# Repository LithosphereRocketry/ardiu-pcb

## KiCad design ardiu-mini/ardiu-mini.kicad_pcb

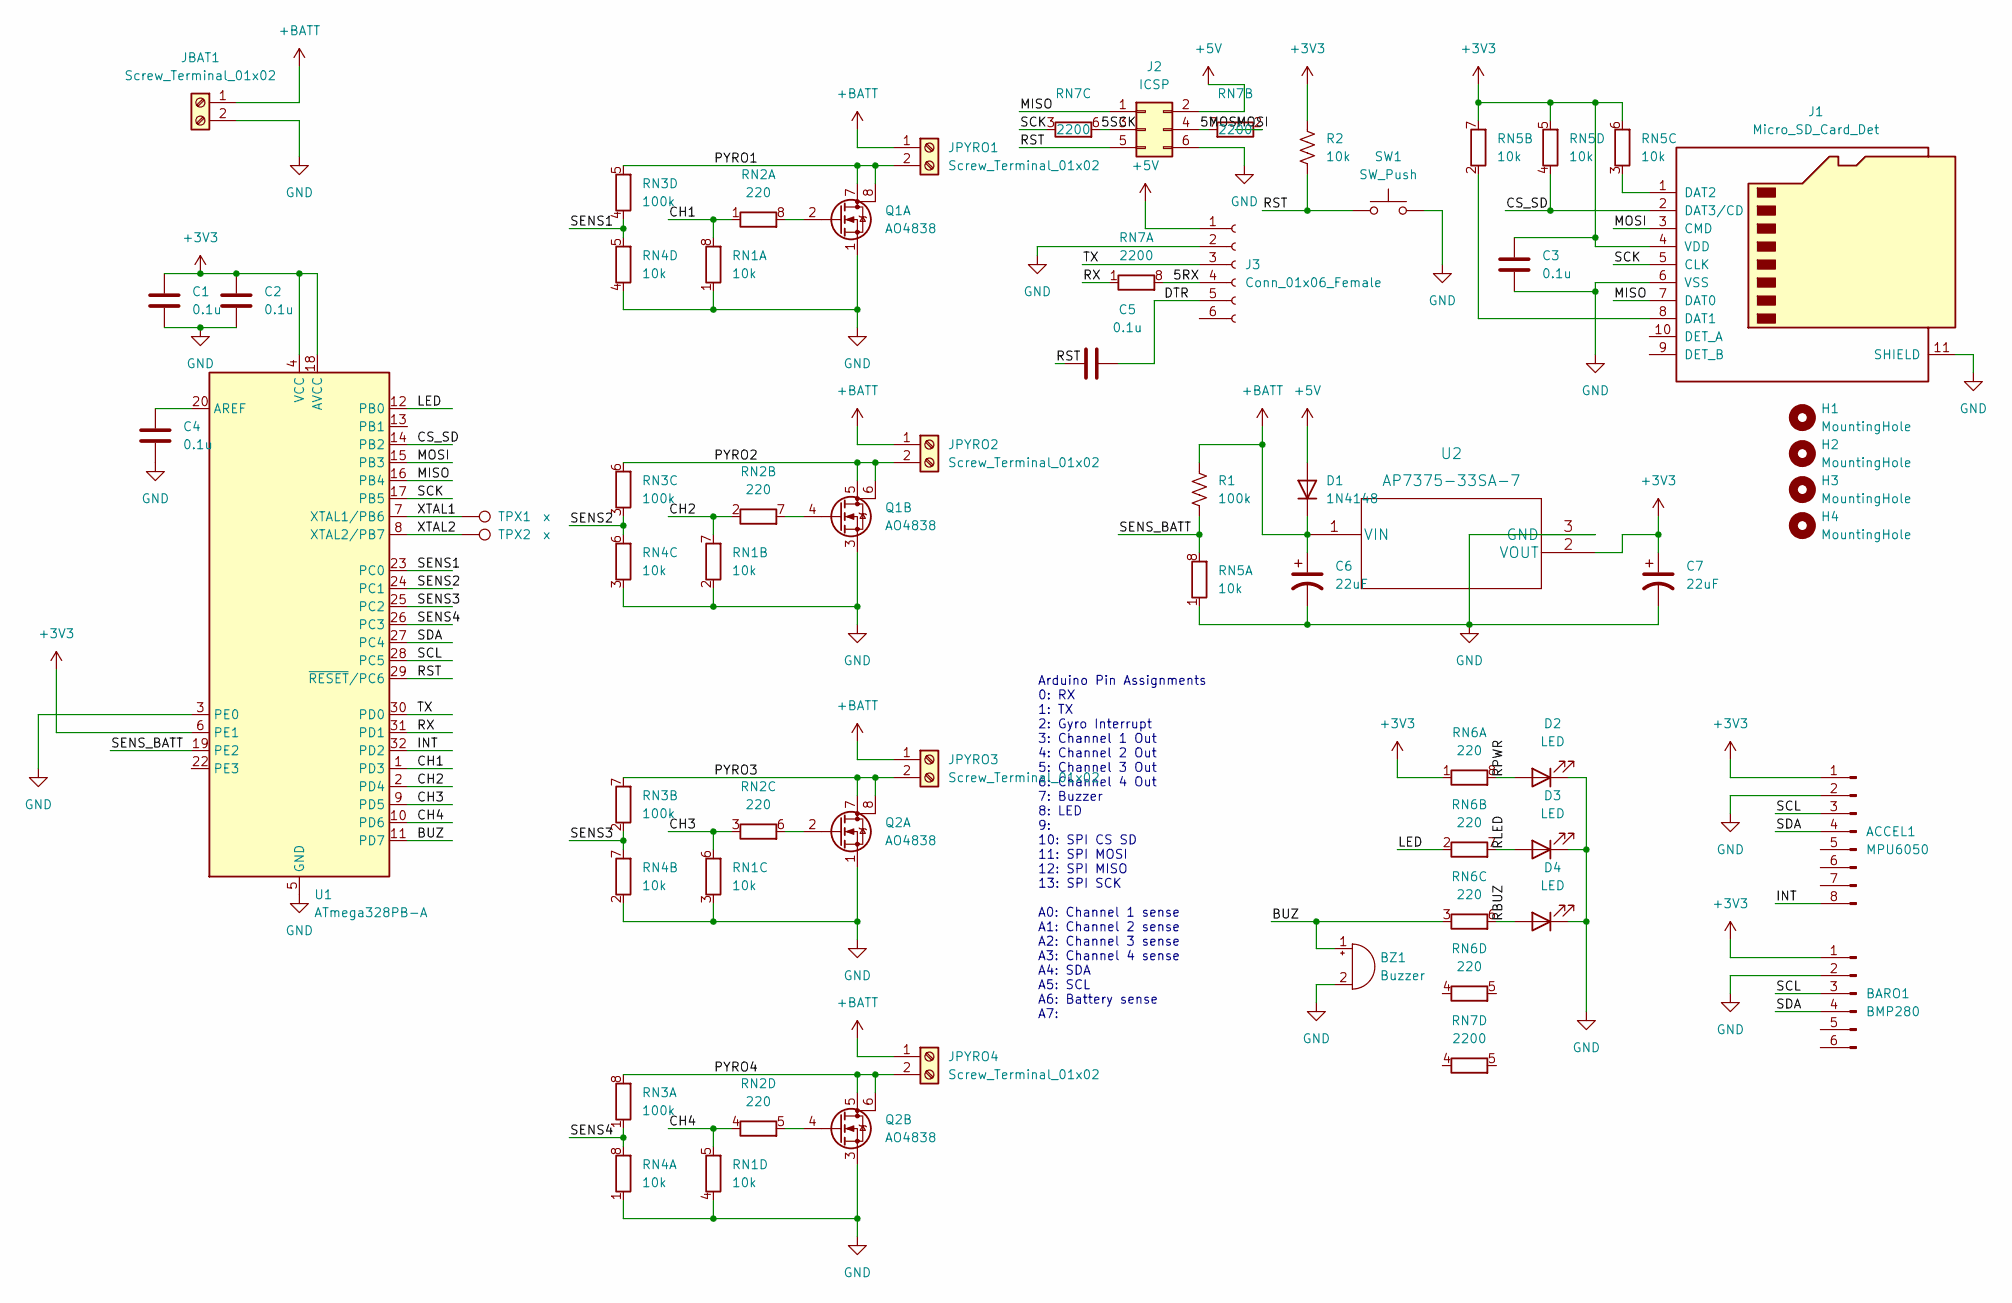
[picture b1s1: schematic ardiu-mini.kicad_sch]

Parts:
ACCEL1: MPU6050; Breakout_MPU6050_Generic
BARO1: BMP280; Breakout_BMP280_Generic
BZ1: Buzzer; Buzzer_12x9.5RM7.6
C1, C2, C3, C4, C5: 0.1u; C_0805_2012Metric_Pad1.18x1.45mm_HandSolder
C6, C7: 22uF; C_1206_3216Metric_Pad1.33x1.80mm_HandSolder
D1: 1N4148; D_DO-35_SOD27_P7.62mm_Horizontal
D2, D3, D4: LED; LED_D3.0mm
H1, H2, H3, H4: MountingHole; MountingHole_3.2mm_M3
J1: Micro_SD_Card_Det; Connector_Amphenol_MicroSD_PushPull
J2: ICSP; PinHeader_2x03_P2.54mm_Vertical
J3: Conn_01x06_Female; PinSocket_1x06_P2.54mm_Vertical
JBAT1: Screw_Terminal_01x02; TerminalBlock_TE_282834-2_1x02_P2.54mm_Horizontal
JPYRO1, JPYRO2, JPYRO3, JPYRO4: Screw_Terminal_01x02; TerminalBlock_TE_282834-2_1x02_P2.54mm_Horizontal
Q1, Q2: AO4838; SO-8_3.9x4.9mm_P1.27mm
R1: 100k; R_0805_2012Metric_Pad1.20x1.40mm_HandSolder
R2: 10k; R_0805_2012Metric_Pad1.20x1.40mm_HandSolder
RN1, RN4, RN5: 10k; R_Array_Concave_4x0603
RN2, RN6: 220; R_Array_Concave_4x0603
RN3: 100k; R_Array_Concave_4x0603
RN7: 2200; R_Array_Concave_4x0603
SW1: SW_Push; SW_PUSH_6mm
TPX1, TPX2: x; TestPoint_Pad_D1.5mm
U1: ATmega328PB-A; TQFP-32_7x7mm_P0.8mm
U2: AP7375-33SA-7; SOT-23_Handsoldering

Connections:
+3V3: ACCEL1.1, BARO1.1, C1.1, C2.1, C3.1, C7.1, J1.4 (VDD), R2.1, RN5.5 (R4.2), RN5.6 (R3.2), RN5.7 (R2.2), RN6.1 (R1.1), U1.4 (VCC), U1.6 (PE1), U1.18 (AVCC), U2.2 (VOUT)
+5V: D1.2 (A), J2.2, J3.1
+BATT: C6.1, D1.1 (K), JBAT1.1, JPYRO1.1, JPYRO2.1, JPYRO3.1, JPYRO4.1, R1.1, U2.1 (VIN)
/5MOSI: J2.4, RN7.7 (R2.2)
/5RX: J3.4, RN7.8 (R1.2)
/5SCK: J2.3, RN7.6 (R3.2)
/BUZ: BZ1.1 (-), RN6.3 (R3.1), U1.11 (PD7)
/CH1: RN1.8 (R1.2), RN2.1 (R1.1), U1.1 (PD3)
/CH2: RN1.7 (R2.2), RN2.2 (R2.1), U1.2 (PD4)
/CH3: RN1.6 (R3.2), RN2.3 (R3.1), U1.9 (PD5)
/CH4: RN1.5 (R4.2), RN2.4 (R4.1), U1.10 (PD6)
/CS_SD: J1.2 (DAT3/CD), RN5.4 (R4.1), U1.14 (PB2)
/DTR: C5.1, J3.5
/INT: ACCEL1.8, U1.32 (PD2)
/LED: RN6.2 (R2.1), U1.12 (PB0)
/MISO: J1.7 (DAT0), J2.1, U1.16 (PB4)
/MOSI: J1.3 (CMD), RN7.2 (R2.1), U1.15 (PB3)
/PYRO1: JPYRO1.2, Q1.7 (D), Q1.8 (D), RN3.5 (R4.2)
/PYRO2: JPYRO2.2, Q1.5 (D), Q1.6 (D), RN3.6 (R3.2)
/PYRO3: JPYRO3.2, Q2.7 (D), Q2.8 (D), RN3.7 (R2.2)
/PYRO4: JPYRO4.2, Q2.5 (D), Q2.6 (D), RN3.8 (R1.2)
/RBUZ: D4.2 (A), RN6.6 (R3.2)
/RLED: D3.2 (A), RN6.7 (R2.2)
/RPWR: D2.2 (A), RN6.8 (R1.2)
/RST: C5.2, J2.5, R2.2, SW1.1, U1.29 (~RESET/PC6)
/RX: RN7.1 (R1.1), U1.31 (PD1)
/SCK: J1.5 (CLK), RN7.3 (R3.1), U1.17 (PB5)
/SCL: ACCEL1.3, BARO1.3, U1.28 (PC5)
/SDA: ACCEL1.4, BARO1.4, U1.27 (PC4)
/SENS1: RN3.4 (R4.1), RN4.5 (R4.2), U1.23 (PC0)
/SENS2: RN3.3 (R3.1), RN4.6 (R3.2), U1.24 (PC1)
/SENS3: RN3.2 (R2.1), RN4.7 (R2.2), U1.25 (PC2)
/SENS4: RN3.1 (R1.1), RN4.8 (R1.2), U1.26 (PC3)
/SENS_BATT: R1.2, RN5.8 (R1.2), U1.19 (PE2)
/TX: J3.3, U1.30 (PD0)
/XTAL1: TPX1.1, U1.7 (XTAL1/PB6)
/XTAL2: TPX2.1, U1.8 (XTAL2/PB7)
GND: ACCEL1.2, BARO1.2, BZ1.2 (+), C1.2, C2.2, C3.2, C4.2, C6.2, C7.2, D2.1 (K), D3.1 (K), D4.1 (K), J1.6 (VSS), J1.11 (SHIELD), J2.6, J3.2, JBAT1.2, Q1.1 (S), Q1.3 (S), Q2.1 (S), Q2.3 (S), RN1.1 (R1.1), RN1.2 (R2.1), RN1.3 (R3.1), RN1.4 (R4.1), RN4.1 (R1.1), RN4.2 (R2.1), RN4.3 (R3.1), RN4.4 (R4.1), RN5.1 (R1.1), SW1.2, U1.3 (PE0), U1.5 (GND), U1.21 (GND), U2.3 (GND)
unnamed: C4.1, U1.20 (AREF)
unnamed: J1.1 (DAT2), RN5.3 (R3.1)
unnamed: J1.8 (DAT1), RN5.2 (R2.1)
unnamed: Q1.2 (G), RN2.8 (R1.2)
unnamed: Q1.4 (G), RN2.7 (R2.2)
unnamed: Q2.2 (G), RN2.6 (R3.2)
unnamed: Q2.4 (G), RN2.5 (R4.2)

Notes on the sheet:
Arduino Pin Assignments 0: RX 1: TX 2: Gyro Interrupt 3: Channel 1 Out 4: Channel 2 Out 5: Channel 3 Out 6: Channel 4 Out 7: Buzzer 8: LED 9: 10: SPI CS SD 11: SPI MOSI 12: SPI MISO 13: SPI SCK A0: Channel 1 sense A1: Channel 2 sense A2: Channel 3 sense A3: Channel 4 sense A4: SDA A5: SCL A6: Batte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

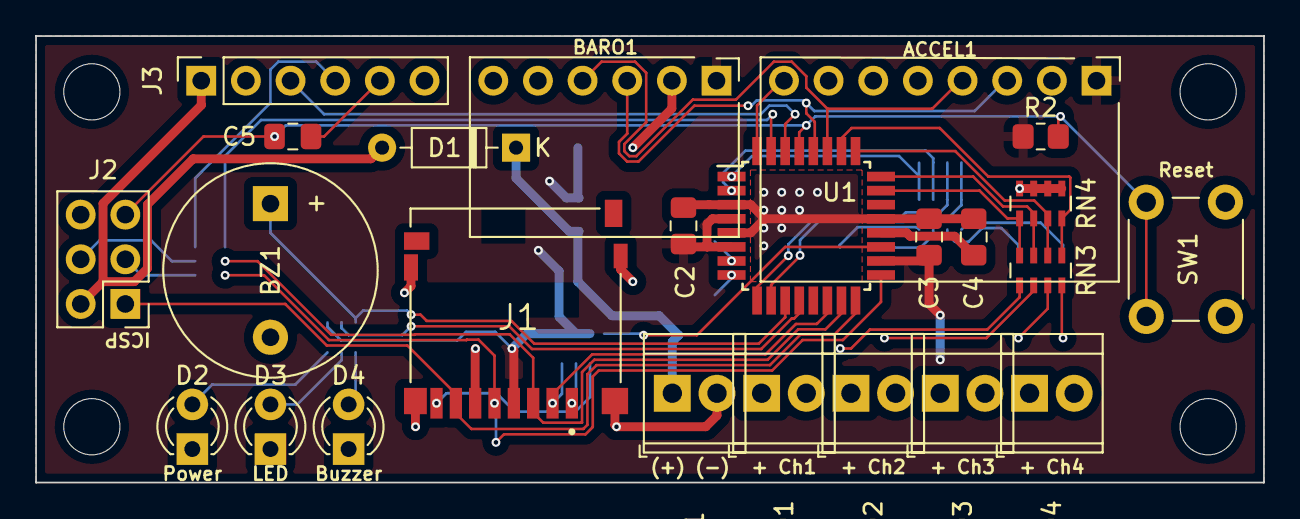
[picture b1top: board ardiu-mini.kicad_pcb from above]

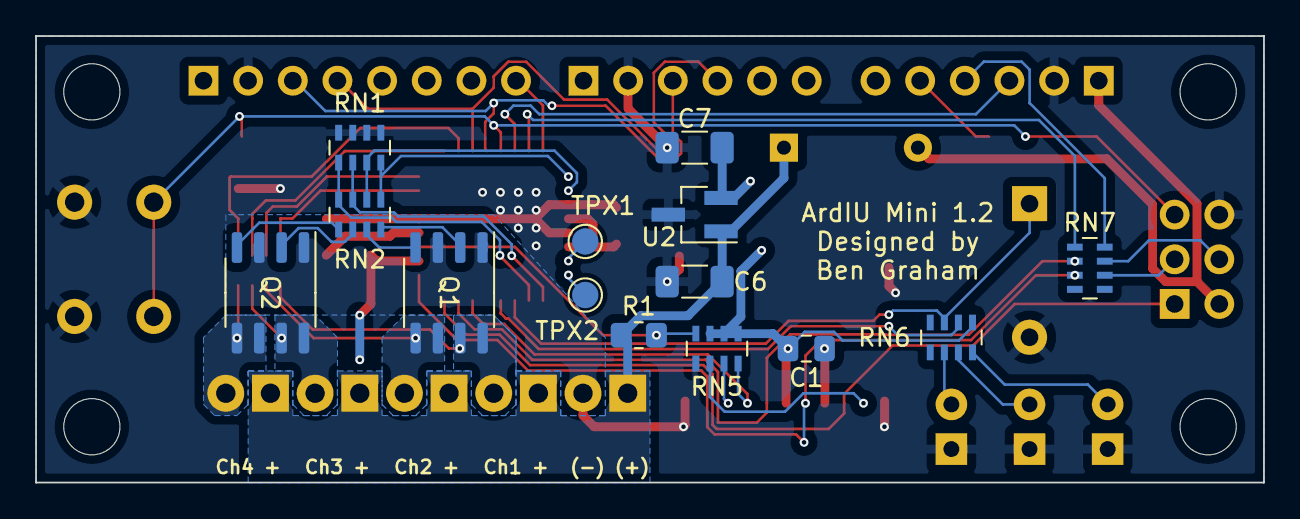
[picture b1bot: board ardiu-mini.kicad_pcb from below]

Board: 2 copper layers, 69.9 x 25.4 mm, 42 parts (14 on the bottom side), 45 nets.

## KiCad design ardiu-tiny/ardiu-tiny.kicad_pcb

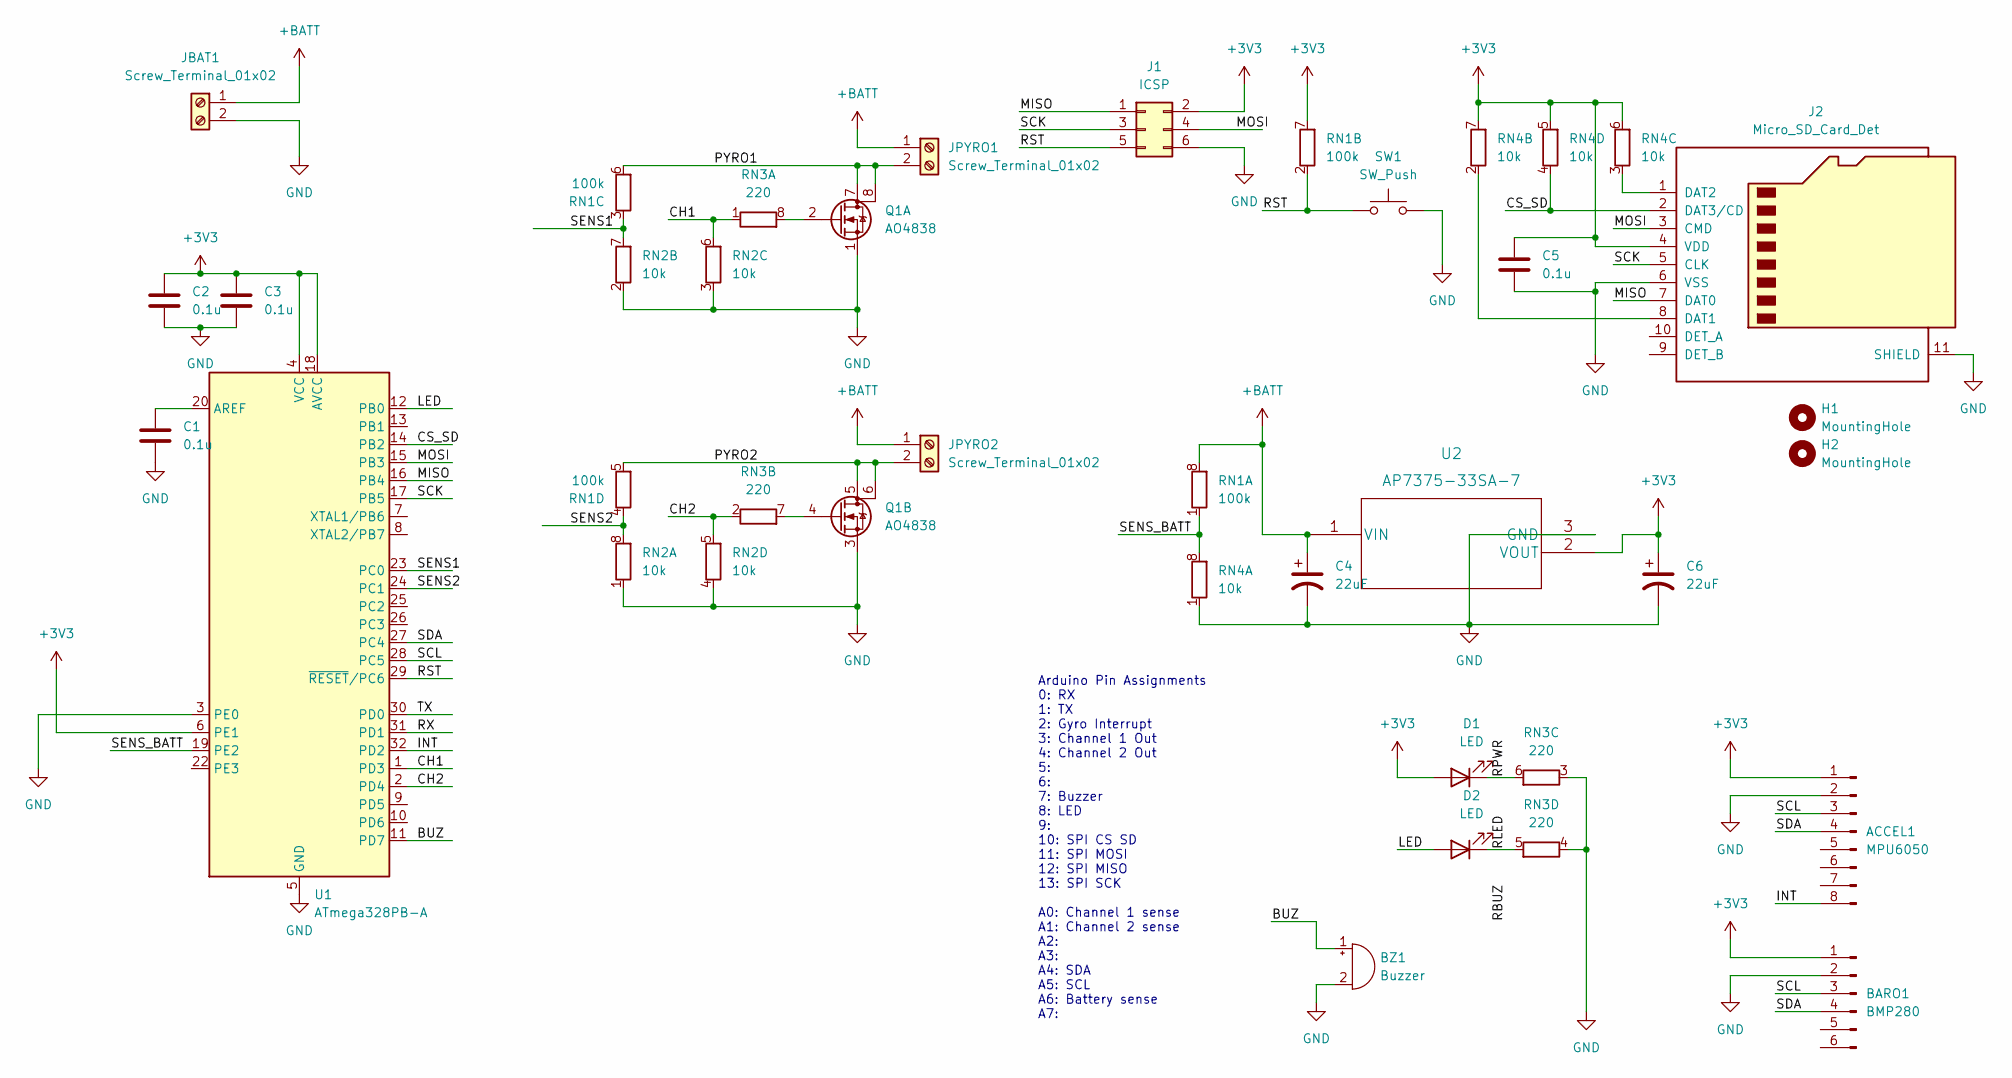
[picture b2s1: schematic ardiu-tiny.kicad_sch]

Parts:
ACCEL1: MPU6050; Breakout_MPU6050_Generic
BARO1: BMP280; Breakout_BMP280_Generic
BZ1: Buzzer; Buzzer_CUI_CPT-9019S-SMT
C1, C2, C3, C5: 0.1u; C_0805_2012Metric_Pad1.18x1.45mm_HandSolder
C4, C6: 22uF; C_1206_3216Metric_Pad1.33x1.80mm_HandSolder
D1, D2: LED; LED_1206_3216Metric_Pad1.42x1.75mm_HandSolder
H1, H2: MountingHole; MountingHole_3.2mm_M3
J1: ICSP; PinHeader_2x03_P2.54mm_Vertical
J2: Micro_SD_Card_Det; Connector_Amphenol_MicroSD_PushPull
JBAT1: Screw_Terminal_01x02; TerminalBlock_TE_282834-2_1x02_P2.54mm_Horizontal
JPYRO1, JPYRO2: Screw_Terminal_01x02; TerminalBlock_TE_282834-2_1x02_P2.54mm_Horizontal
Q1: AO4838; SO-8_3.9x4.9mm_P1.27mm
RN1: 100k; R_Array_Concave_4x0603
RN2, RN4: 10k; R_Array_Concave_4x0603
RN3: 220; R_Array_Concave_4x0603
SW1: SW_Push; SW_Push_Rect_5mm
U1: ATmega328PB-A; TQFP-32_7x7mm_P0.8mm
U2: AP7375-33SA-7; SOT-23_Handsoldering

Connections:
+3V3: ACCEL1.1, BARO1.1, C2.1, C3.1, C5.1, C6.1, D1.2 (A), J1.2, J2.4 (VDD), RN1.7 (R2.2), RN4.5 (R4.2), RN4.6 (R3.2), RN4.7 (R2.2), U1.4 (VCC), U1.6 (PE1), U1.18 (AVCC), U2.2 (VOUT)
+BATT: C4.1, JBAT1.1, JPYRO1.1, JPYRO2.1, RN1.8 (R1.2), U2.1 (VIN)
/BUZ: BZ1.1 (-), U1.11 (PD7)
/CH1: RN2.6 (R3.2), RN3.1 (R1.1), U1.1 (PD3)
/CH2: RN2.5 (R4.2), RN3.2 (R2.1), U1.2 (PD4)
/CS_SD: J2.2 (DAT3/CD), RN4.4 (R4.1), U1.14 (PB2)
/INT: ACCEL1.8, U1.32 (PD2)
/LED: D2.2 (A), U1.12 (PB0)
/MISO: J1.1, J2.7 (DAT0), U1.16 (PB4)
/MOSI: J1.4, J2.3 (CMD), U1.15 (PB3)
/PYRO1: JPYRO1.2, Q1.7 (D), Q1.8 (D), RN1.6 (R3.2)
/PYRO2: JPYRO2.2, Q1.5 (D), Q1.6 (D), RN1.5 (R4.2)
/RLED: D2.1 (K), RN3.5 (R4.2)
/RPWR: D1.1 (K), RN3.6 (R3.2)
/RST: J1.5, RN1.2 (R2.1), SW1.1, U1.29 (~RESET/PC6)
/RX: U1.31 (PD1)
/SCK: J1.3, J2.5 (CLK), U1.17 (PB5)
/SCL: ACCEL1.3, BARO1.3, U1.28 (PC5)
/SDA: ACCEL1.4, BARO1.4, U1.27 (PC4)
/SENS1: RN1.3 (R3.1), RN2.7 (R2.2), U1.23 (PC0)
/SENS2: RN1.4 (R4.1), RN2.8 (R1.2), U1.24 (PC1)
/SENS_BATT: RN1.1 (R1.1), RN4.8 (R1.2), U1.19 (PE2)
/TX: U1.30 (PD0)
GND: ACCEL1.2, BARO1.2, BZ1.2 (+), C1.2, C2.2, C3.2, C4.2, C5.2, C6.2, J1.6, J2.6 (VSS), J2.11 (SHIELD), JBAT1.2, Q1.1 (S), Q1.3 (S), RN2.1 (R1.1), RN2.2 (R2.1), RN2.3 (R3.1), RN2.4 (R4.1), RN3.3 (R3.1), RN3.4 (R4.1), RN4.1 (R1.1), SW1.2, U1.3 (PE0), U1.5 (GND), U1.21 (GND), U2.3 (GND)
unnamed: J2.8 (DAT1), RN4.2 (R2.1)
unnamed: J2.1 (DAT2), RN4.3 (R3.1)
unnamed: Q1.2 (G), RN3.8 (R1.2)
unnamed: Q1.4 (G), RN3.7 (R2.2)
unnamed: C1.1, U1.20 (AREF)

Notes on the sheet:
Arduino Pin Assignments 0: RX 1: TX 2: Gyro Interrupt 3: Channel 1 Out 4: Channel 2 Out 5: 6: 7: Buzzer 8: LED 9: 10: SPI CS SD 11: SPI MOSI 12: SPI MISO 13: SPI SCK A0: Channel 1 sense A1: Channel 2 sense A2: A3: A4: SDA A5: SCL A6: Battery sense A7:

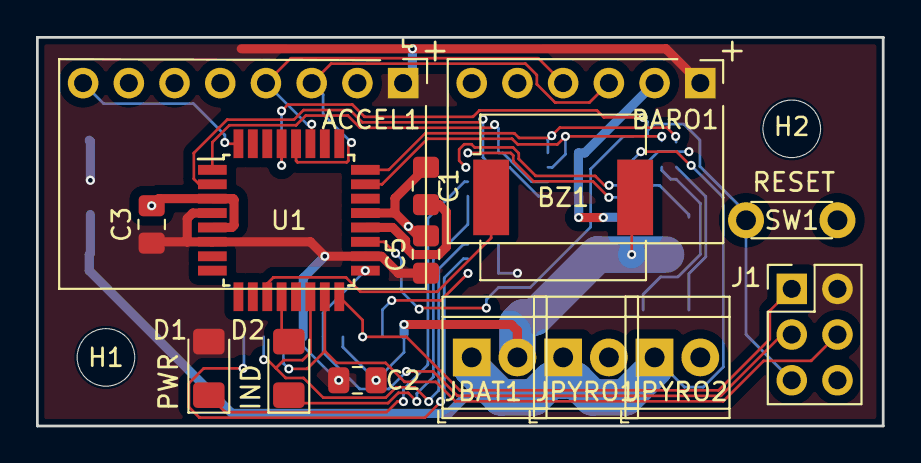
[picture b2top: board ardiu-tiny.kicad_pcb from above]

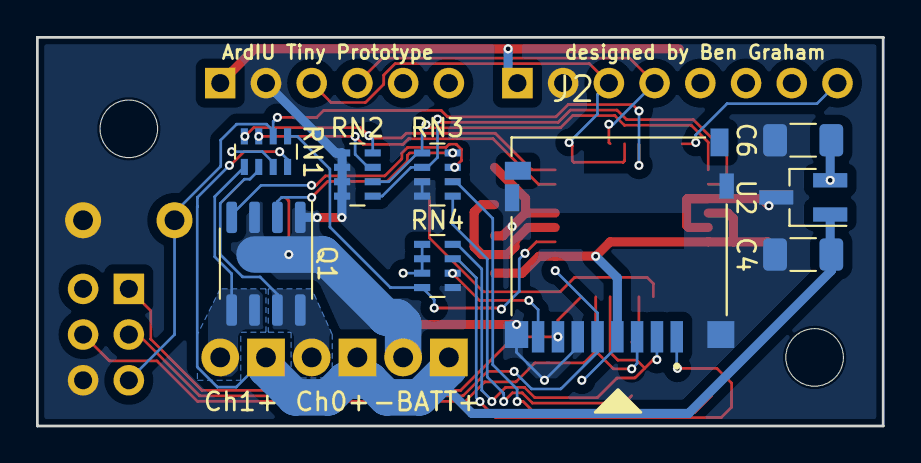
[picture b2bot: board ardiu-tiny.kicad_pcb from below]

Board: 2 copper layers, 47.0 x 21.6 mm, 26 parts (9 on the bottom side), 27 nets.

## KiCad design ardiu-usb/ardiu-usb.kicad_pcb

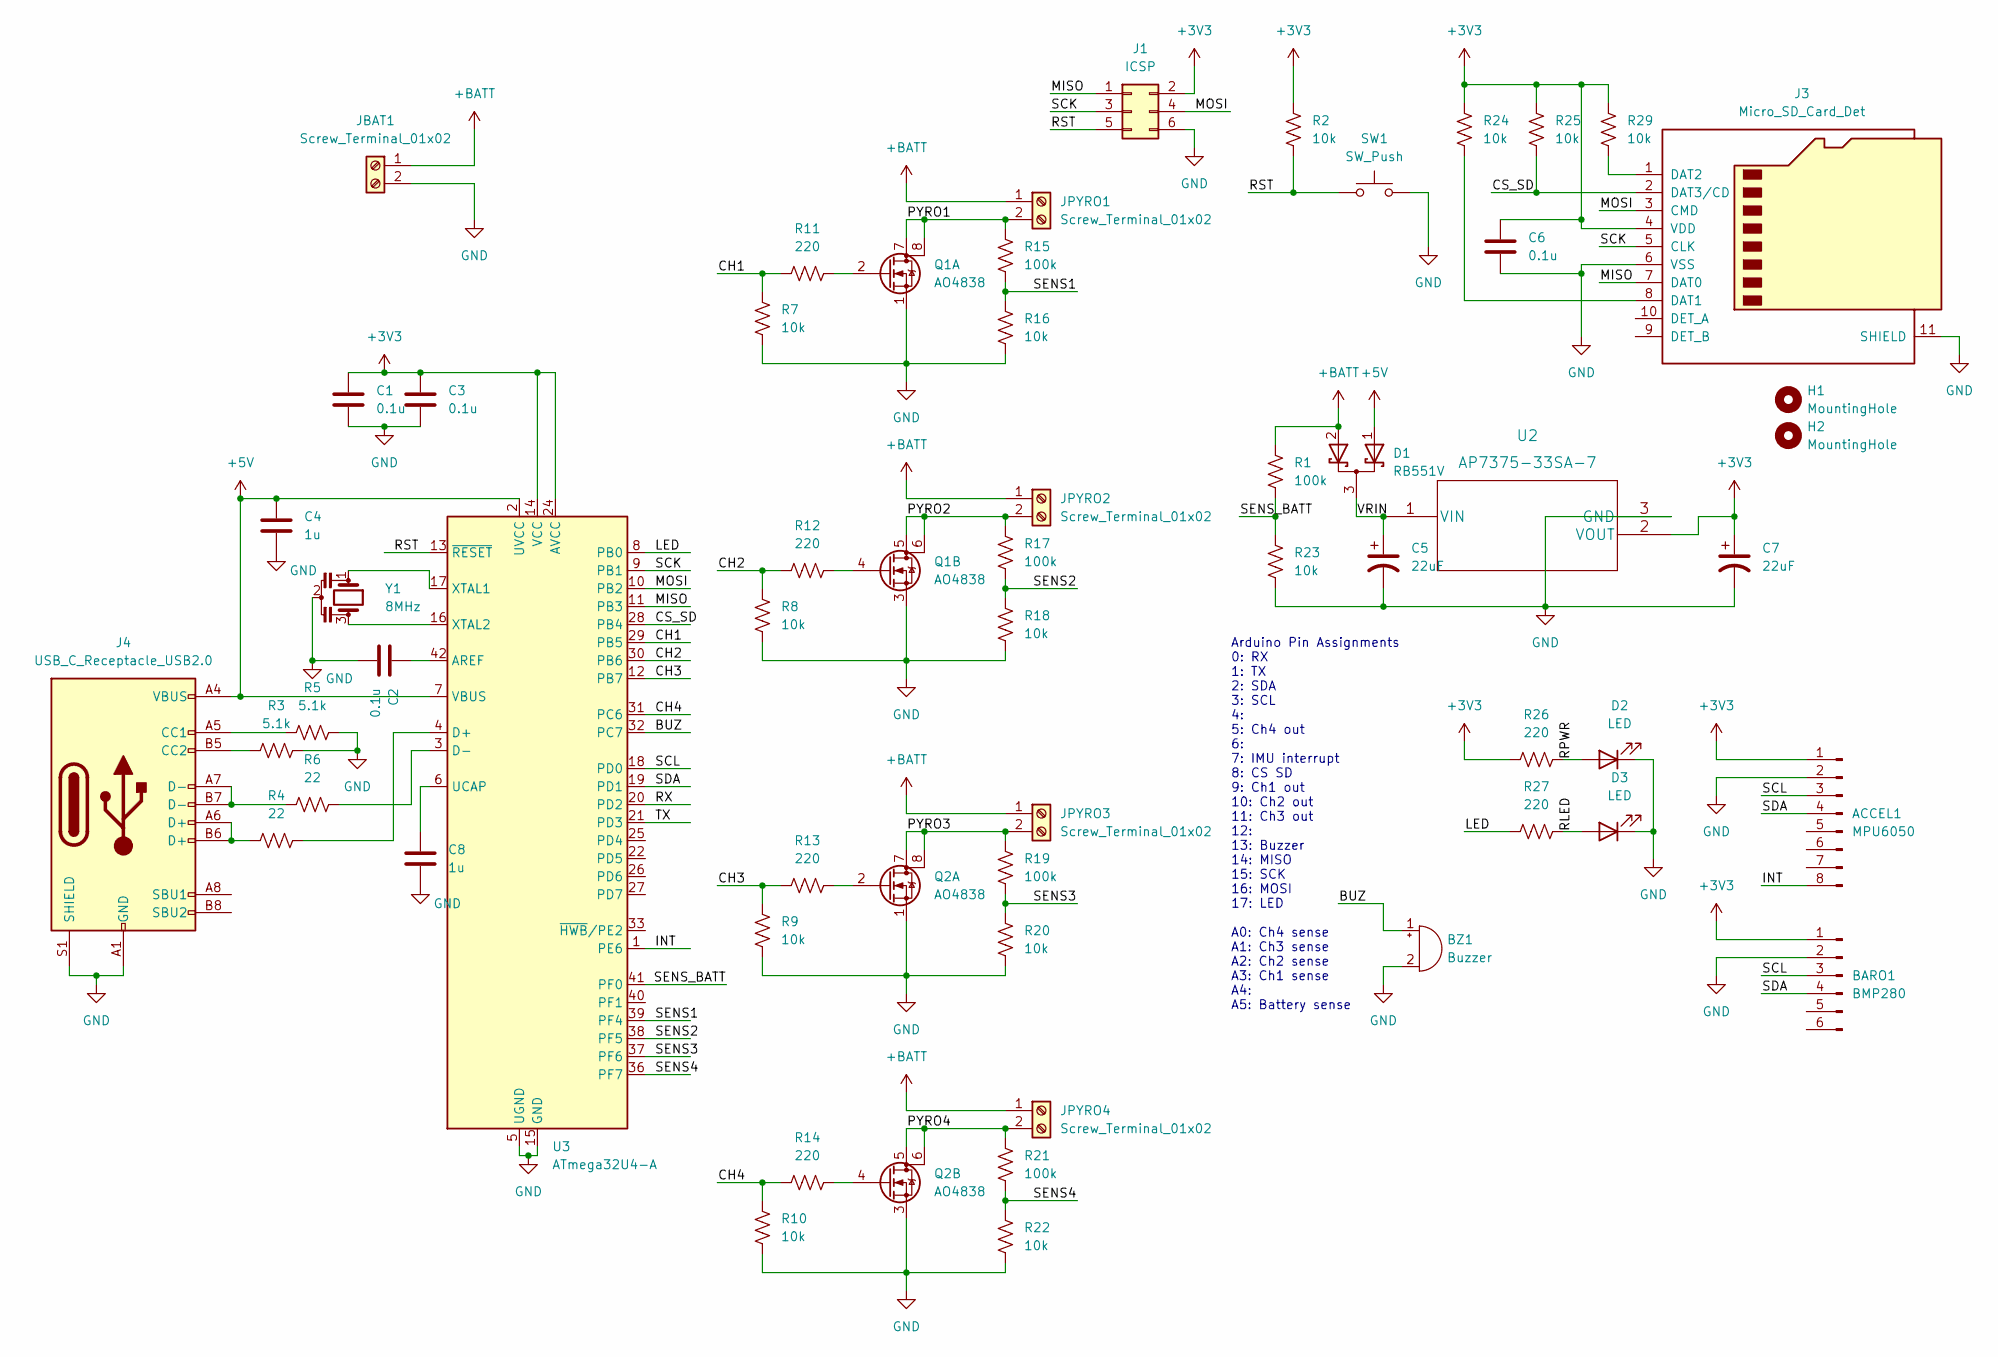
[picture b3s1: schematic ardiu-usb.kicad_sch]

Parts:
ACCEL1: MPU6050; Breakout_MPU6050_Generic
BARO1: BMP280; Breakout_BMP280_Generic
BZ1: Buzzer; Buzzer_12x9.5RM7.6
C1, C2, C3, C6: 0.1u; C_0805_2012Metric_Pad1.18x1.45mm_HandSolder
C4, C8: 1u; C_0805_2012Metric_Pad1.18x1.45mm_HandSolder
C5, C7: 22uF; C_1206_3216Metric_Pad1.33x1.80mm_HandSolder
D1: RB551V; SOT-23_Handsoldering
D2, D3: LED; LED_D3.0mm
H1, H2: MountingHole; MountingHole_3.2mm_M3
J1: ICSP; PinHeader_2x03_P2.54mm_Vertical
J3: Micro_SD_Card_Det; Connector_Amphenol_MicroSD_PushPull
J4: USB_C_Receptacle_USB2.0; USB_C_Receptacle_GCT_USB4085
JBAT1: Screw_Terminal_01x02; TerminalBlock_TE_282834-2_1x02_P2.54mm_Horizontal
JPYRO1, JPYRO2, JPYRO3, JPYRO4: Screw_Terminal_01x02; TerminalBlock_TE_282834-2_1x02_P2.54mm_Horizontal
Q1, Q2: AO4838; SO-8_3.9x4.9mm_P1.27mm
R1, R15, R17, R19, R21: 100k; R_0805_2012Metric_Pad1.20x1.40mm_HandSolder
R2, R7, R8, R9, R10, R16, R18, R20, R22, R23, R24, R25, R29: 10k; R_0805_2012Metric_Pad1.20x1.40mm_HandSolder
R3, R5: 5.1k; R_0805_2012Metric_Pad1.20x1.40mm_HandSolder
R4, R6: 22; R_0805_2012Metric_Pad1.20x1.40mm_HandSolder
R11, R12, R13, R14, R26, R27: 220; R_0805_2012Metric_Pad1.20x1.40mm_HandSolder
SW1: SW_Push; SW_PUSH_6mm
U2: AP7375-33SA-7; SOT-23_Handsoldering
U3: ATmega32U4-A; TQFP-44_10x10mm_P0.8mm
Y1: 8MHz; Resonator_SMD_Murata_CSTxExxV-3Pin_3.0x1.1mm_HandSoldering

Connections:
+3V3: ACCEL1.1, BARO1.1, C1.1, C3.1, C6.1, C7.1, J1.2, J3.4 (VDD), R2.1, R24.1, R25.1, R26.1, R29.1, U2.2 (VOUT), U3.14 (VCC), U3.24 (AVCC), U3.34 (VCC), U3.44 (AVCC)
+5V: C4.1, D1.1 (K), J4.A4 (VBUS), J4.A9 (VBUS), J4.B4 (VBUS), J4.B9 (VBUS), U3.2 (UVCC), U3.7 (VBUS)
+BATT: D1.2 (K), JBAT1.1, JPYRO1.1, JPYRO2.1, JPYRO3.1, JPYRO4.1, R1.1
/BUZ: BZ1.1 (-), U3.32 (PC7)
/CH1: R7.1, R11.1, U3.29 (PB5)
/CH2: R8.1, R12.1, U3.30 (PB6)
/CH3: R9.1, R13.1, U3.12 (PB7)
/CH4: R10.1, R14.1, U3.31 (PC6)
/CS_SD: J3.2 (DAT3/CD), R25.2, U3.28 (PB4)
/INT: ACCEL1.8, U3.1 (PE6)
/LED: R27.1, U3.8 (PB0)
/MISO: J1.1, J3.7 (DAT0), U3.11 (PB3)
/MOSI: J1.4, J3.3 (CMD), U3.10 (PB2)
/PYRO1: JPYRO1.2, Q1.7 (D), Q1.8 (D), R15.1
/PYRO2: JPYRO2.2, Q1.5 (D), Q1.6 (D), R17.1
/PYRO3: JPYRO3.2, Q2.7 (D), Q2.8 (D), R19.1
/PYRO4: JPYRO4.2, Q2.5 (D), Q2.6 (D), R21.1
/RLED: D3.2 (A), R27.2
/RPWR: D2.2 (A), R26.2
/RST: J1.5, R2.2, SW1.1, U3.13 (~RESET)
/RX: U3.20 (PD2)
/SCK: J1.3, J3.5 (CLK), U3.9 (PB1)
/SCL: ACCEL1.3, BARO1.3, U3.18 (PD0)
/SDA: ACCEL1.4, BARO1.4, U3.19 (PD1)
/SENS1: R15.2, R16.1, U3.39 (PF4)
/SENS2: R17.2, R18.1, U3.38 (PF5)
/SENS3: R19.2, R20.1, U3.37 (PF6)
/SENS4: R21.2, R22.1, U3.36 (PF7)
/SENS_BATT: R1.2, R23.1, U3.41 (PF0)
/TX: U3.21 (PD3)
/VRIN: C5.1, D1.3 (A), U2.1 (VIN)
GND: ACCEL1.2, BARO1.2, BZ1.2 (+), C1.2, C2.2, C3.2, C4.2, C5.2, C6.2, C7.2, C8.2, D2.1 (K), D3.1 (K), J1.6, J3.6 (VSS), J3.11 (SHIELD), J4.A1 (GND), J4.A12 (GND), J4.B1 (GND), J4.B12 (GND), J4.S1 (SHIELD), JBAT1.2, Q1.1 (S), Q1.3 (S), Q2.1 (S), Q2.3 (S), R3.2, R5.2, R7.2, R8.2, R9.2, R10.2, R16.2, R18.2, R20.2, R22.2, R23.2, SW1.2, U2.3 (GND), U3.5 (UGND), U3.15 (GND), U3.23 (GND), U3.35 (GND), U3.43 (GND), Y1.2
unnamed: C2.1, U3.42 (AREF)
unnamed: C8.1, U3.6 (UCAP)
unnamed: J3.1 (DAT2), R29.2
unnamed: J3.8 (DAT1), R24.2
unnamed: J4.A5 (CC1), R5.1
unnamed: J4.A6 (D+), J4.B6 (D+), R4.1
unnamed: J4.A7 (D-), J4.B7 (D-), R6.1
unnamed: J4.B5 (CC2), R3.1
unnamed: Q1.2 (G), R11.2
unnamed: Q1.4 (G), R12.2
unnamed: Q2.2 (G), R13.2
unnamed: Q2.4 (G), R14.2
unnamed: R4.2, U3.4 (D+)
unnamed: R6.2, U3.3 (D-)
unnamed: U3.16 (XTAL2), Y1.3
unnamed: U3.17 (XTAL1), Y1.1

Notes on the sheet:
Arduino Pin Assignments 0: RX 1: TX 2: SDA 3: SCL 4: 5: Ch4 out 6: 7: IMU interrupt 8: CS SD 9: Ch1 out 10: Ch2 out 11: Ch3 out 12: 13: Buzzer 14: MISO 15: SCK 16: MOSI 17: LED A0: Ch4 sense A1: Ch3 sense A2: Ch2 sense A3: Ch1 sense A4: A5: Battery sense

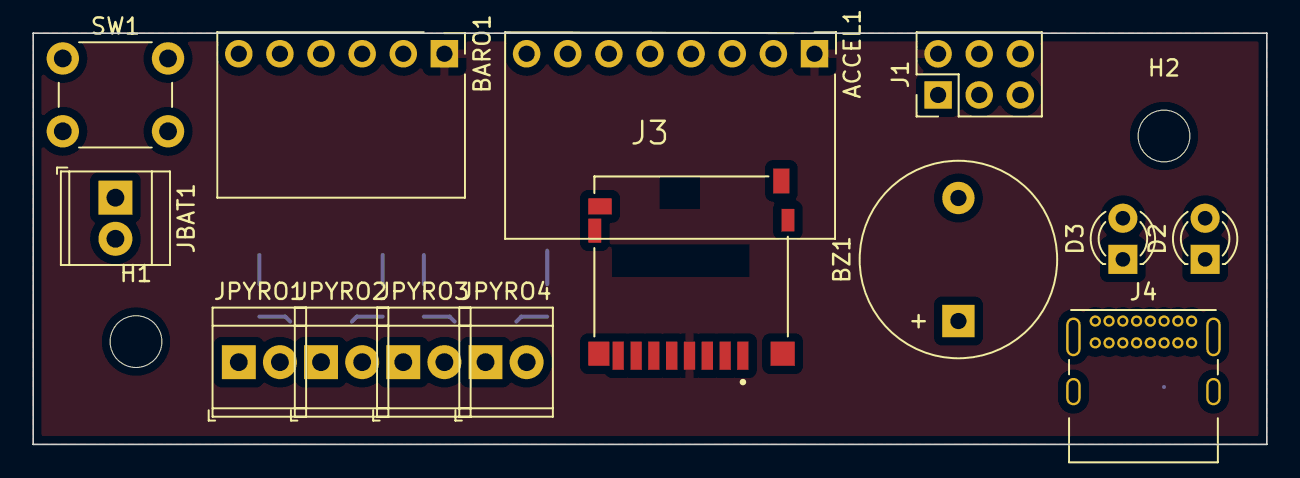
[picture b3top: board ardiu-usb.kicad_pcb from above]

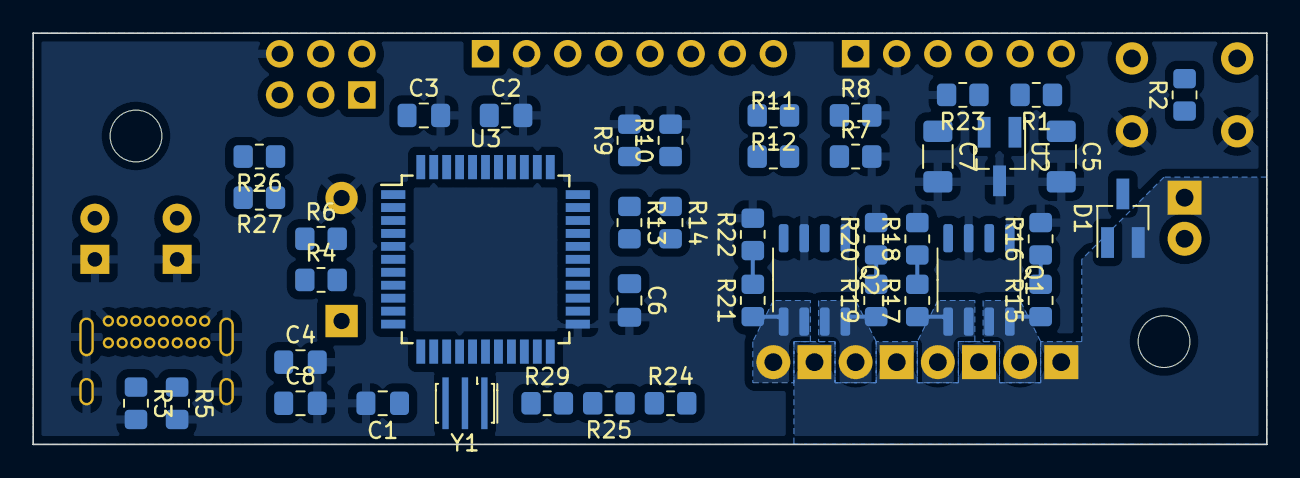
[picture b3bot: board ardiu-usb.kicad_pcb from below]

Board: 2 copper layers, 76.2 x 25.4 mm, 58 parts (42 on the bottom side), 46 nets.

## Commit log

2022-10-02 Initial files for ArdIU Mini
2022-10-06 Board layout with weak grounding path
2022-12-30 Fixed some errors, added actually 5V safe debug ports
2023-09-26 Started USB variant with 32U4
2023-12-11 Mini ext libs
2023-12-11 Ardiu USB progress
2024-04-11 Ardiu tiny
